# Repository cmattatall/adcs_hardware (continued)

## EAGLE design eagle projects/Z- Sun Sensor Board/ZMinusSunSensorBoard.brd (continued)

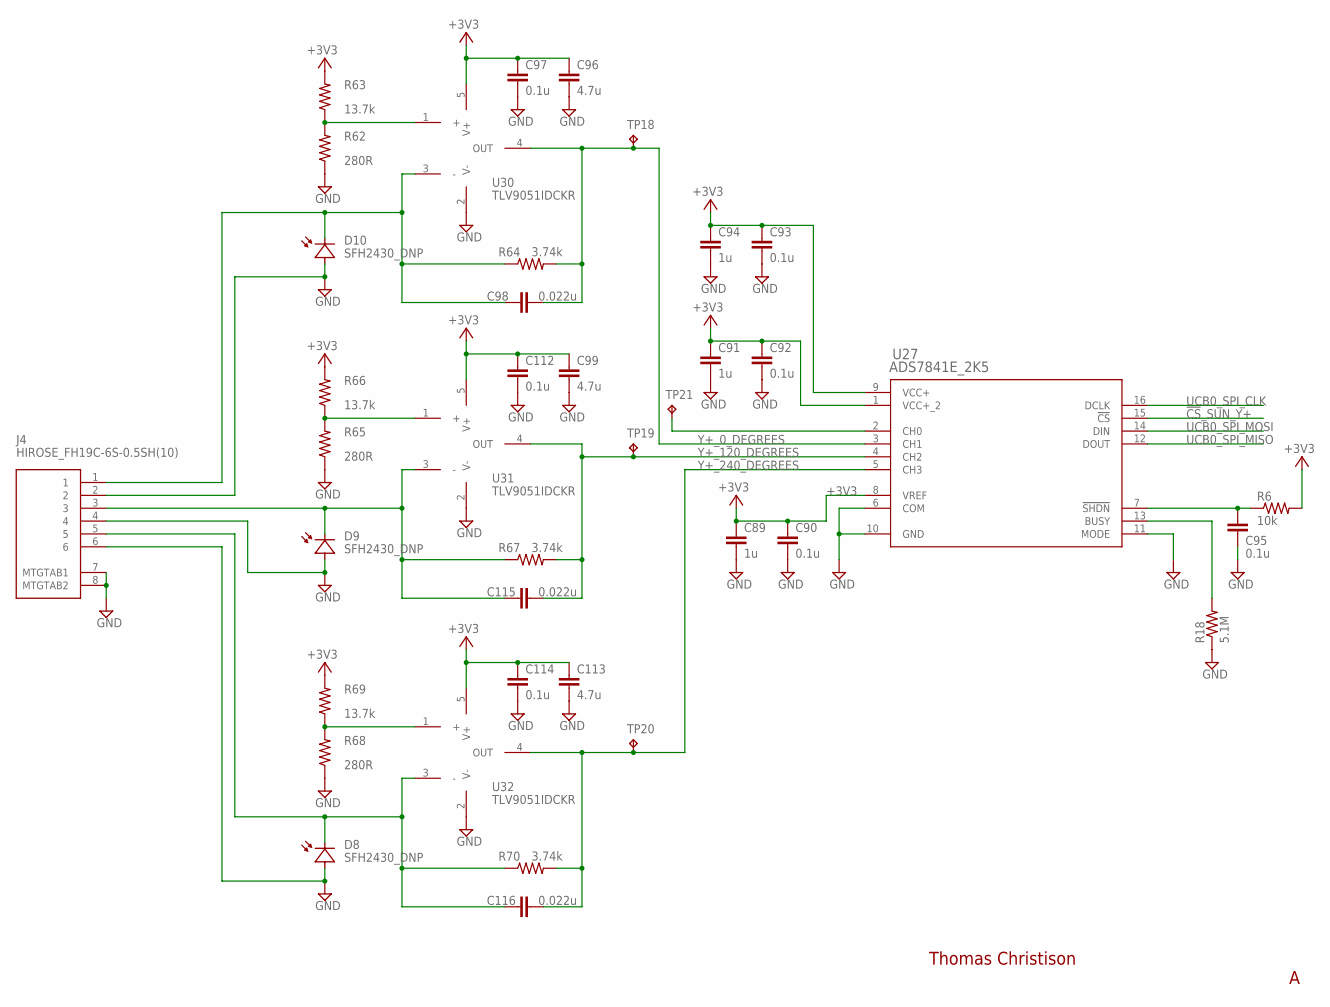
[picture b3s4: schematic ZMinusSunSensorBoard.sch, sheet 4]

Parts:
C89, C91, C94: 1u; C0402
C90, C92, C93, C95, C97, C112, C114: 0.1u; C0402
C96, C99, C113: 4.7u; C0402
C98, C115, C116: 0.022u; C0402
J4: HIROSE_FH19C-6S-0.5SH(10)
R6: 10k; R0402
R18: 5.1M; R0402
R62, R65, R68: 280R; R0402
R63, R66, R69: 13.7k; R0402
R64, R67, R70: 3.74k; R0402
TP18, TP19, TP20, TP21: TESTPOINT; TP_P76H50
U27: ADS7841E_2K5; DBQ16
U30, U31, U32: TLV9051IDCKR; SC70-5P65_210X110L36X22N_TLV9051

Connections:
!CS!_SUN_Y+: U27.15 (!CS); also elsewhere on the board
+3V3: C89.1, C90.1, C91.1, C92.1, C93.1, C94.1, C96.1, C97.1, C99.1, C112.1, C113.1, C114.1, R6.2, R63.2, R66.2, R69.2, U27.1 (VCC+_2), U27.8 (VREF), U27.9 (VCC+), U30.5 (V+), U31.5 (V+), U32.5 (V+); also elsewhere on the board
GND: C89.2, C90.2, C91.2, C92.2, C93.2, C94.2, C95.2, C96.2, C97.2, C99.2, C112.2, C113.2, C114.2, J4.2, J4.4, J4.6, J4.7 (MTGTAB1), J4.8 (MTGTAB2), R18.1, R62.1, R65.1, R68.1, U27.6 (COM), U27.10 (GND), U27.11 (MODE), U30.2 (V-), U31.2 (V-), U32.2 (V-); also elsewhere on the board
unnamed: TP21.1, U27.2 (CH0)
unnamed: C95.1, R6.1, U27.7 (!SHDN)
unnamed: C98.1, J4.1, R64.1, U30.3 (-)
unnamed: R18.2, U27.13 (BUSY)
unnamed: R62.2, R63.1, U30.1 (+)
unnamed: C115.1, J4.3, R67.1, U31.3 (-)
unnamed: R65.2, R66.1, U31.1 (+)
unnamed: C116.1, J4.5, R70.1, U32.3 (-)
unnamed: R68.2, R69.1, U32.1 (+)
UCB0_SPI_CLK: U27.16 (DCLK); also elsewhere on the board
UCB0_SPI_MISO: U27.12 (DOUT); also elsewhere on the board
UCB0_SPI_MOSI: U27.14 (DIN); also elsewhere on the board
Y+_0_DEGREES: C98.2, R64.2, TP18.1, U27.3 (CH1), U30.4 (OUT)
Y+_120_DEGREES: C115.2, R67.2, TP19.1, U27.4 (CH2), U31.4 (OUT)
Y+_240_DEGREES: C116.2, R70.2, TP20.1, U27.5 (CH3), U32.4 (OUT)

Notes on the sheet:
Thomas Christison

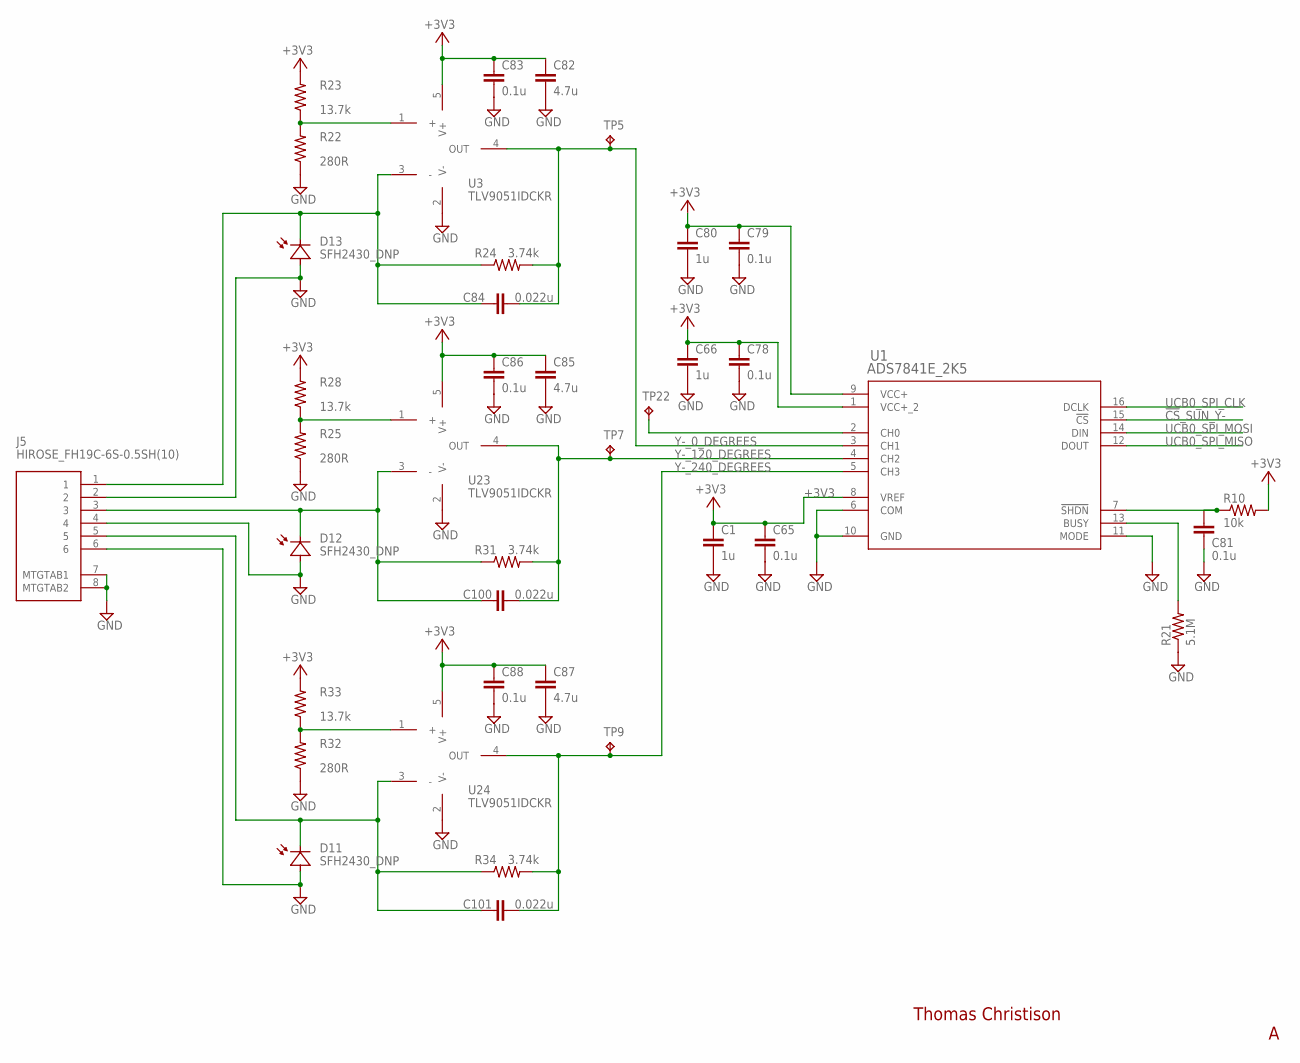
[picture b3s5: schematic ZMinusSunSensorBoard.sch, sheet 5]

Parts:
C1, C66, C80: 1u; C0402
C65, C78, C79, C81, C83, C86, C88: 0.1u; C0402
C82, C85, C87: 4.7u; C0402
C84, C100, C101: 0.022u; C0402
J5: HIROSE_FH19C-6S-0.5SH(10)
R10: 10k; R0402
R21: 5.1M; R0402
R22, R25, R32: 280R; R0402
R23, R28, R33: 13.7k; R0402
R24, R31, R34: 3.74k; R0402
TP5, TP7, TP9, TP22: TESTPOINT; TP_P76H50
U1: ADS7841E_2K5; DBQ16
U3, U23, U24: TLV9051IDCKR; SC70-5P65_210X110L36X22N_TLV9051

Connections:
!CS!_SUN_Y-: U1.15 (!CS); also elsewhere on the board
+3V3: C1.1, C65.1, C66.1, C78.1, C79.1, C80.1, C82.1, C83.1, C85.1, C86.1, C87.1, C88.1, R10.2, R23.2, R28.2, R33.2, U1.1 (VCC+_2), U1.8 (VREF), U1.9 (VCC+), U3.5 (V+), U23.5 (V+), U24.5 (V+); also elsewhere on the board
GND: C1.2, C65.2, C66.2, C78.2, C79.2, C80.2, C81.2, C82.2, C83.2, C85.2, C86.2, C87.2, C88.2, J5.2, J5.4, J5.6, J5.7 (MTGTAB1), J5.8 (MTGTAB2), R21.1, R22.1, R25.1, R32.1, U1.6 (COM), U1.10 (GND), U1.11 (MODE), U3.2 (V-), U23.2 (V-), U24.2 (V-); also elsewhere on the board
unnamed: TP22.1, U1.2 (CH0)
unnamed: C100.1, J5.3, R31.1, U23.3 (-)
unnamed: C81.1, R10.1, U1.7 (!SHDN)
unnamed: C84.1, J5.1, R24.1, U3.3 (-)
unnamed: R22.2, R23.1, U3.1 (+)
unnamed: R25.2, R28.1, U23.1 (+)
unnamed: C101.1, J5.5, R34.1, U24.3 (-)
unnamed: R32.2, R33.1, U24.1 (+)
unnamed: R21.2, U1.13 (BUSY)
UCB0_SPI_CLK: U1.16 (DCLK); also elsewhere on the board
UCB0_SPI_MISO: U1.12 (DOUT); also elsewhere on the board
UCB0_SPI_MOSI: U1.14 (DIN); also elsewhere on the board
Y-_0_DEGREES: C84.2, R24.2, TP5.1, U1.3 (CH1), U3.4 (OUT)
Y-_120_DEGREES: C100.2, R31.2, TP7.1, U1.4 (CH2), U23.4 (OUT)
Y-_240_DEGREES: C101.2, R34.2, TP9.1, U1.5 (CH3), U24.4 (OUT)

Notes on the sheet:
Thomas Christison

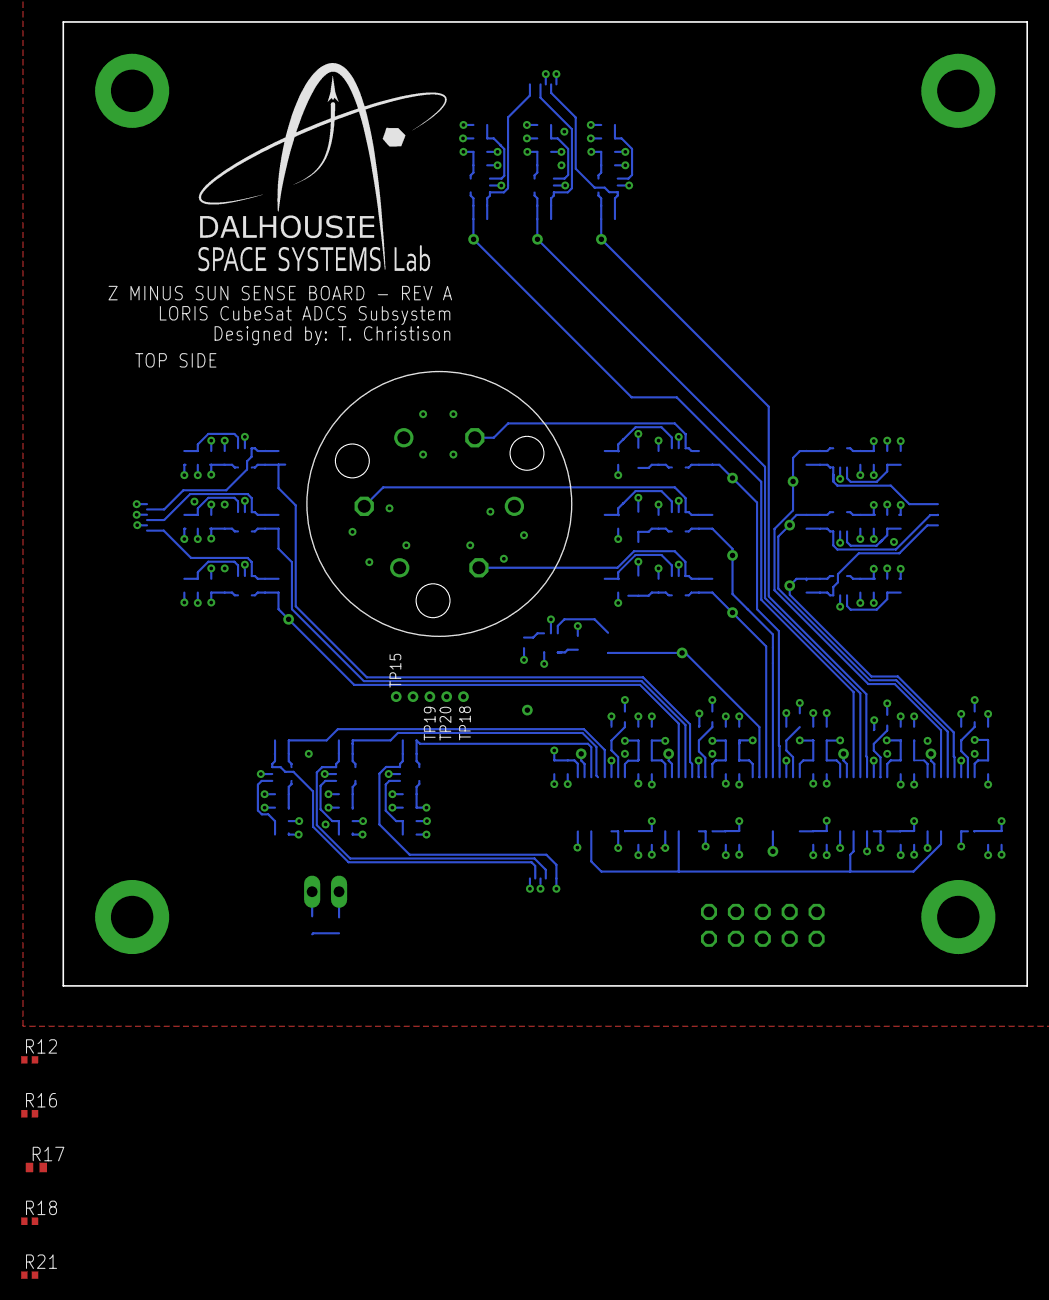
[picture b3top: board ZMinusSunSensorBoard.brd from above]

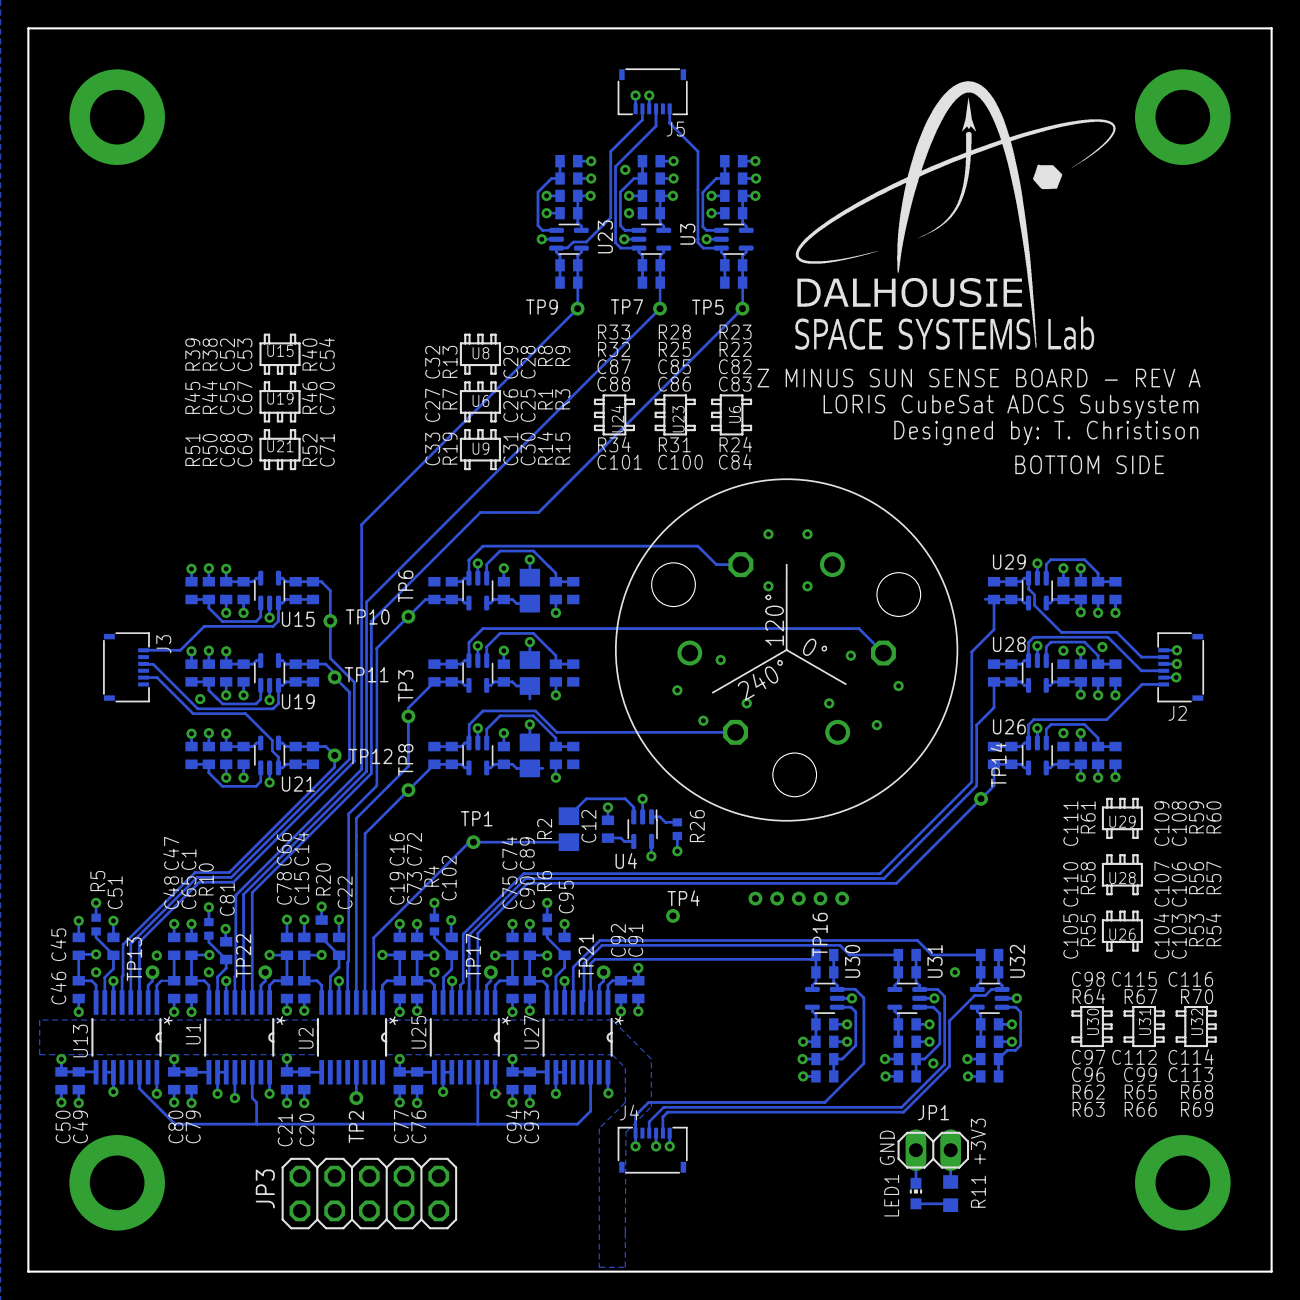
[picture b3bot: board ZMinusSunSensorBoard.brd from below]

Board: 2 copper layers, 91.0 x 91.0 mm, 194 parts (180 on the bottom side), 72 nets.

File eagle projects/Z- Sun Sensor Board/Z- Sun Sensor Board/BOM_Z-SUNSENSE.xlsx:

LORIS ADCS |  |  |  | BILL OF MATERIALS
BOARD: Z- SUN SENSE BOARD |  |  |  | REVISION: A | Date: 2021.01.28
Item | Qty | MPN | Reference Designator | Value | Footprint | Description | Package | Datasheet
1 | 1 | DO NOT POPULATE | A1 | DO NOT POPULATE | Custom | Sun Sensor Mount | SUN_SENOR_MASK | -
2 | 3 | VJ0402Y103KXJAC31 | C14, C16, C21 | 1u | 0402 | CAP CER 10000PF 16V X7R 0402 | C0402 | https://www.vishay.com/docs/45040/vj31vj34automlcc.pdf
3 | 8 | CS0402KRX7R8BB104 | C12, C15, C19, C20, C22, C26, C29, C31 | 0.1u | 0402 | CAP CER 0.1UF 25V X7R 0402 | C0402 | https://www.yageo.com/upload/media/product/productsearch/dat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
4 | 3 | CL21B475KOFNNNE | C25, C28, C30 | 4.7u | 0805 | CAP CER 4.7UF 16V X7R 0805 | C0805 | https://media.digikey.com/pdf/Data%20Sheets/Samsung%20PDFs/C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
5 | 3 | AC0402KRX7R8BB223 | C27, C32, C33 | 0.022u | 0402 | CAP CER 0.022UF 25V X7R 0402 | C0402 | https://www.yageo.com/upload/media/product/productsearch/dat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
6 | 3 | DO NOT POPULATE | J4, J5, J6 | DO NOT POPULATE | DO NOT POPULATE | Terminal Block Connector 1x02 | 2POL254 | -
7 | 1 | DO NOT POPULATE | JP3 | DO NOT POPULATE | DO NOT POPULATE | PIN HEADER | 1X06 | -
8 | 3 | RC0402FR-07280RL | R1, R8, R14 | 280R | 0402 | RES SMD 280 OHM 1% 1/16W 0402 | R0402 | https://www.yageo.com/upload/media/product/productsearch/dat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
9 | 1 | RC0805JR-070RL | R2 | 0R | 0805 | RES SMD 0 OHM JUMPER 1/8W 0805 | R0805 | https://www.yageo.com/upload/media/product/productsearch/dat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
10 | 1 | RE0402FRE0710KL | R20 | 10k | 0402 | RES SMD 10K OHM 1% 1/16W 0402 | R0402 | https://www.yageo.com/upload/media/product/productsearch/dat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
11 | 1 | RC0402JR-075M1L | R26 | 5.1M | 0402 | RES SMD 5.1M OHM 5% 1/16W 0402 | R0603 | https://www.yageo.com/upload/media/product/productsearch/dat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
12 | 3 | RC0402FR-0713K7L | R3, R9, R15 | 13.7k | 0402 | RES SMD 13.7K OHM 1% 1/16W 0402 | R0402 | https://www.yageo.com/upload/media/product/productsearch/dat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
13 | 3 | RC0402FR-073K74L | R7, R13, R19 | 3.74k | 0402 | RES SMD 3.74K OHM 1% 1/16W 0402 | R0402 | https://www.yageo.com/upload/media/product/productsearch/dat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
14 | 1 | ADS7841E | U2 | ADS7841E_2K5 | 16-SSOP | 12 Bit Analog to Digital Converter 4 Input 1 SAR 16-SSOP | DBQ16 | http://www.ti.com/lit/gpn/ADS7841
15 | 1 | LM20BIM7X | U4 | LM20BIM7X_NOPB | SC-70-5 | Temperature Sensor Analog, Local -55°C ~ 130°C 11.77mV/°C SC-70-5 | SOT23-5P65_210X110L40X22N_LM20 | https://www.ti.com/lit/ds/symlink/lm20.pdf?ts=1611799060094&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
16 | 3 | TLV9051IDCKR | U6, U8, U9 | TLV9051IDCKR | SC-70-5 | General Purpose Amplifier 1 Circuit Rail-to-Rail SC-70-5 | SC70-5P65_210X110L36X22N_TLV9051 | https://www.ti.com/lit/ds/symlink/tlv9051.pdf?HQS=dis-dk-nul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

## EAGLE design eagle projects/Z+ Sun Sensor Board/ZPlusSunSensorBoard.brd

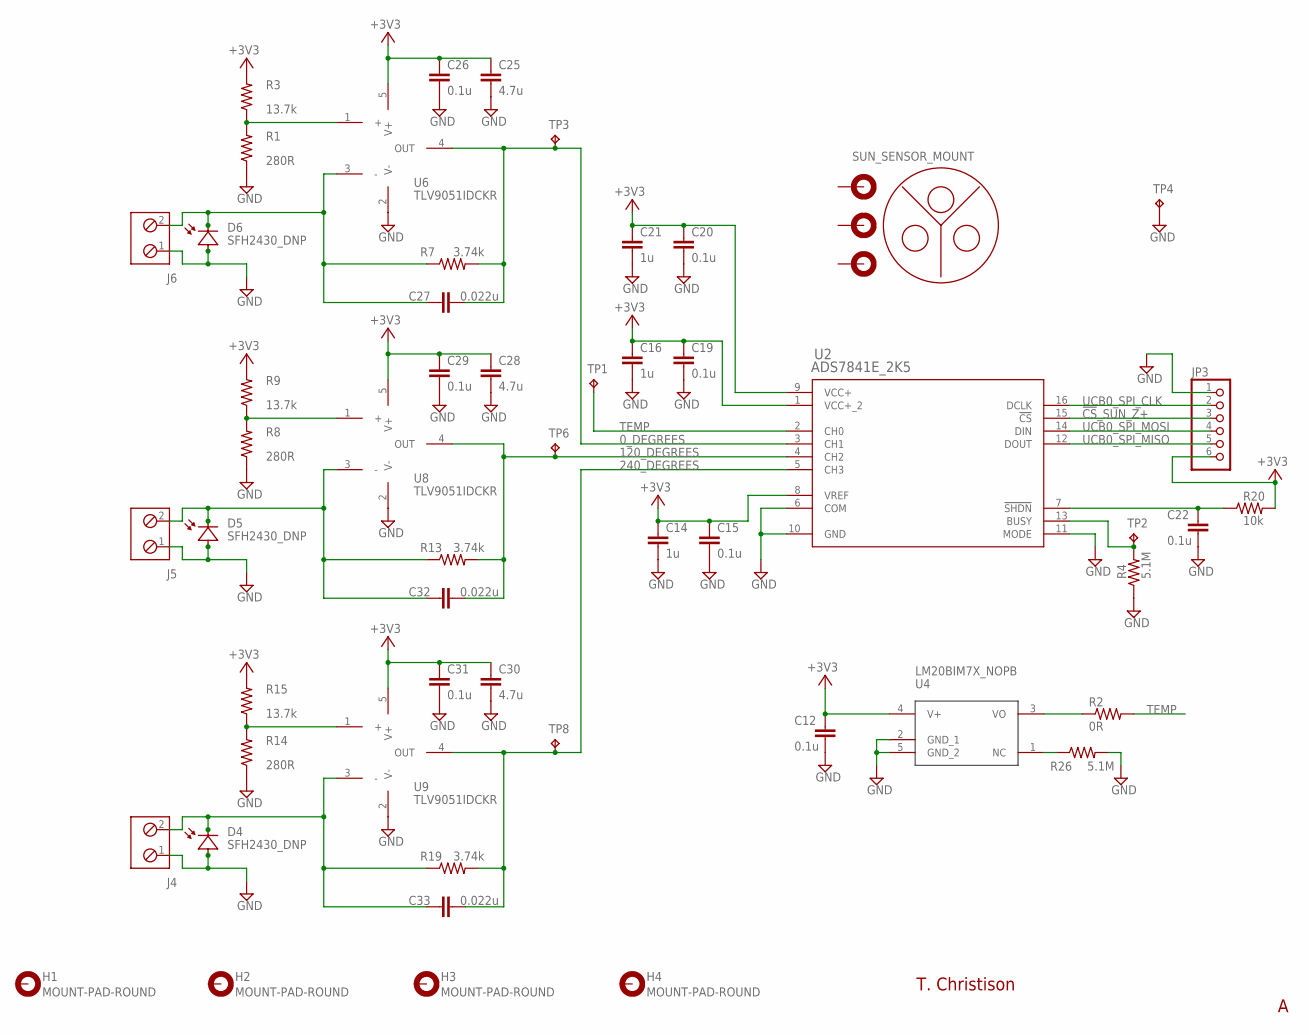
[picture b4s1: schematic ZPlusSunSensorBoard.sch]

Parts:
A1: SUN_SENSOR_MOUNT; SUN_SENOR_MASK
C12, C15, C19, C20, C22, C26, C29, C31: 0.1u; C0402
C14, C16, C21: 1u; C0402
C25, C28, C30: 4.7u; C0805
C27, C32, C33: 0.022u; C0402
H1, H2, H3, H4: MOUNT-PAD-ROUND; PC104
J4, J5, J6: TRM_BLK_1X2; 2POL254
JP3: PINHD-1X6; 1X06
R1, R8, R14: 280R; R0402
R2: 0R; R0805
R3, R9, R15: 13.7k; R0402
R4, R26: 5.1M; R0402
R7, R13, R19: 3.74k; R0402
R20: 10k; R0402
TP1, TP2, TP3, TP4, TP6, TP8: TESTPOINT; TP_P76H50
U2: ADS7841E_2K5; DBQ16
U4: LM20BIM7X_NOPB; SOT23-5P65_210X110L40X22N_LM20
U6, U8, U9: TLV9051IDCKR; SC70-5P65_210X110L36X22N_TLV9051

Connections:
0_DEGREES: C27.2, R7.2, TP3.1, U2.3 (CH1), U6.4 (OUT)
120_DEGREES: C32.2, R13.2, TP6.1, U2.4 (CH2), U8.4 (OUT)
240_DEGREES: C33.2, R19.2, TP8.1, U2.5 (CH3), U9.4 (OUT)
!CS!_SUN_Z+: JP3.3, U2.15 (!CS)
+3V3: C12.1, C14.1, C15.1, C16.1, C19.1, C20.1, C21.1, C25.1, C26.1, C28.1, C29.1, C30.1, C31.1, JP3.6, R3.2, R9.2, R15.2, R20.2, U2.1 (VCC+_2), U2.8 (VREF), U2.9 (VCC+), U4.4 (V+), U6.5 (V+), U8.5 (V+), U9.5 (V+)
GND: C12.2, C14.2, C15.2, C16.2, C19.2, C20.2, C21.2, C22.2, C25.2, C26.2, C28.2, C29.2, C30.2, C31.2, J4.1, J5.1, J6.1, JP3.1, R1.1, R4.1, R8.1, R14.1, R26.2, TP4.1, U2.6 (COM), U2.10 (GND), U2.11 (MODE), U4.2 (GND_1), U4.5 (GND_2), U6.2 (V-), U8.2 (V-), U9.2 (V-)
unnamed: R2.1, U4.3 (VO)
unnamed: R4.2, TP2.1, U2.13 (BUSY)
unnamed: C27.1, J6.2, R7.1, U6.3 (-)
unnamed: R1.2, R3.1, U6.1 (+)
unnamed: R26.1, U4.1 (NC)
unnamed: C32.1, J5.2, R13.1, U8.3 (-)
unnamed: R8.2, R9.1, U8.1 (+)
unnamed: C33.1, J4.2, R19.1, U9.3 (-)
unnamed: R14.2, R15.1, U9.1 (+)
unnamed: C22.1, R20.1, U2.7 (!SHDN)
TEMP: R2.2, TP1.1, U2.2 (CH0)
UCB0_SPI_CLK: JP3.2, U2.16 (DCLK)
UCB0_SPI_MISO: JP3.5, U2.12 (DOUT)
UCB0_SPI_MOSI: JP3.4, U2.14 (DIN)

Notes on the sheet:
T. Christison

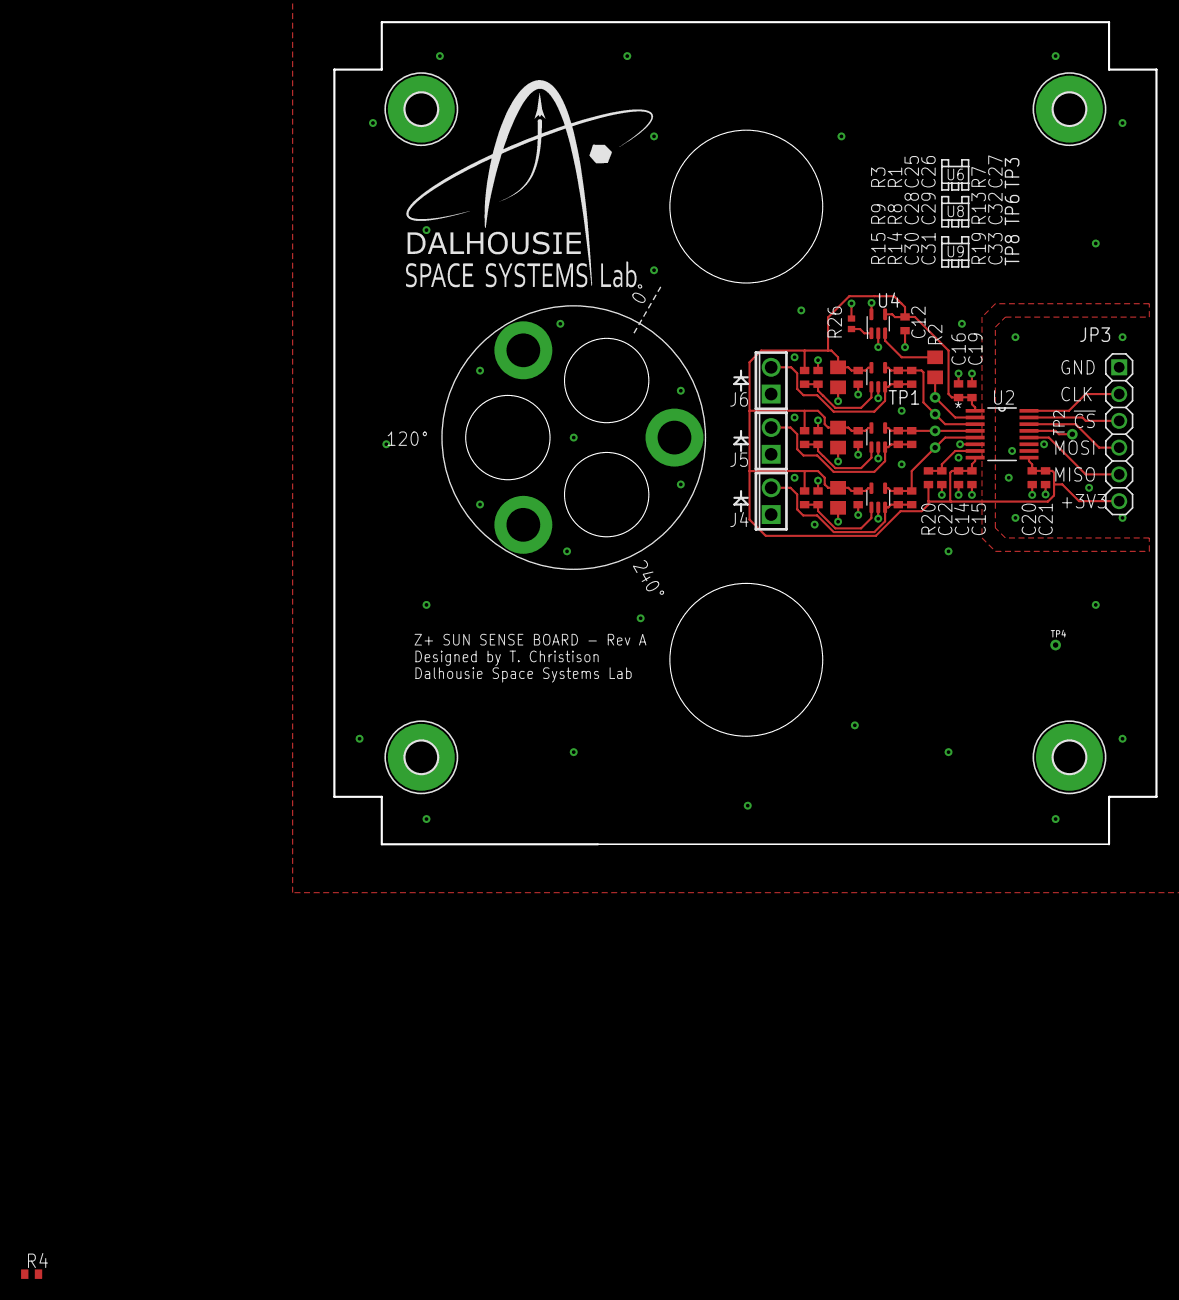
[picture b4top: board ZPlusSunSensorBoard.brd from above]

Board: 2 copper layers, 78.0 x 78.0 mm, 51 parts (0 on the bottom side), 20 nets.

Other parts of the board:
DRILEGEND: DRILEGEND

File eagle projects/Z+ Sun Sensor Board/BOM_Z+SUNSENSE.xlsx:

LORIS ADCS |  |  |  | BILL OF MATERIALS
BOARD: Z+ SUN SENSE BOARD |  |  |  | REV A | Date: 2021.02.14
Item | Qty | MPN | Reference Designator | Value | Footprint | Description | Datasheet
1 | 1 | DO NOT POPULATE | A1 | DO NOT POPULATE | Custom | Sun Sensor Mount | -
2 | 3 | VJ0402Y103KXJAC31 | C14, C16, C21 | 1u | C0402 | CAP CER 10000PF 16V X7R 0402 | https://www.vishay.com/docs/45040/vj31vj34automlcc.pdf
3 | 8 | CS0402KRX7R8BB104 | C12, C15, C19, C20, C22, C26, C29, C31 | 0.1u | C0402 | CAP CER 0.1UF 25V X7R 0402 | https://www.yageo.com/upload/media/product/productsearch/dat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
4 | 3 | CL21B475KOFNNNE | C25, C28, C30 | 4.7u | C0805 | CAP CER 4.7UF 16V X7R 0805 | https://media.digikey.com/pdf/Data%20Sheets/Samsung%20PDFs/C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
5 | 3 | AC0402KRX7R8BB223 | C27, C32, C33 | 0.022u | C0402 | CAP CER 0.022UF 25V X7R 0402 | https://www.yageo.com/upload/media/product/productsearch/dat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
6 | 3 | DO NOT POPULATE | J4, J5, J6 | DO NOT POPULATE | DO NOT POPULATE | Terminal Block Connector 1x02 | -
7 | 1 | DO NOT POPULATE | JP3 | DO NOT POPULATE | DO NOT POPULATE | PIN HEADER | -
8 | 3 | RC0402FR-07280RL | R1, R8, R14 | 280R | R0402 | RES SMD 280 OHM 1% 1/16W 0402 | https://www.yageo.com/upload/media/product/productsearch/dat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
9 | 1 | RC0805JR-070RL | R2 | 0R | R0805 | RES SMD 0 OHM JUMPER 1/8W 0805 | https://www.yageo.com/upload/media/product/productsearch/dat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
10 | 1 | RE0402FRE0710KL | R20 | 10k | R0402 | RES SMD 10K OHM 1% 1/16W 0402 | https://www.yageo.com/upload/media/product/productsearch/dat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
11 | 1 | RC0402JR-075M1L | R26 | 5.1M | R0402 | RES SMD 5.1M OHM 5% 1/16W 0402 | https://www.yageo.com/upload/media/product/productsearch/dat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
12 | 3 | RC0402FR-0713K7L | R3, R9, R15 | 13.7k | R0402 | RES SMD 13.7K OHM 1% 1/16W 0402 | https://www.yageo.com/upload/media/product/productsearch/dat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
13 | 3 | RC0402FR-073K74L | R7, R13, R19 | 5.6k | R0402 | RES SMD 3.74K OHM 1% 1/16W 0402 | https://www.yageo.com/upload/media/product/productsearch/dat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
14 | 1 | ADS7841E | U2 | ADS7841E_2K5 | DBQ16 | 12 Bit Analog to Digital Converter 4 Input 1 SAR 16-SSOP | http://www.ti.com/lit/gpn/ADS7841
15 | 1 | LM20BIM7X | U4 | LM20BIM7X_NOPB | SOT23-5P65_210X110L40X22N_LM20 | Temperature Sensor Analog, Local -55°C ~ 130°C 11.77mV/°C SC-70-5 | https://www.ti.com/lit/ds/symlink/lm20.pdf?ts=1611799060094&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
16 | 3 | TLV9051IDCKR | U6, U8, U9 | TLV9051IDCKR | SC70-5P65_210X110L36X22N_TLV9051 | General Purpose Amplifier 1 Circuit Rail-to-Rail SC-70-5 | https://www.ti.com/lit/ds/symlink/tlv9051.pdf?HQS=dis-dk-nul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

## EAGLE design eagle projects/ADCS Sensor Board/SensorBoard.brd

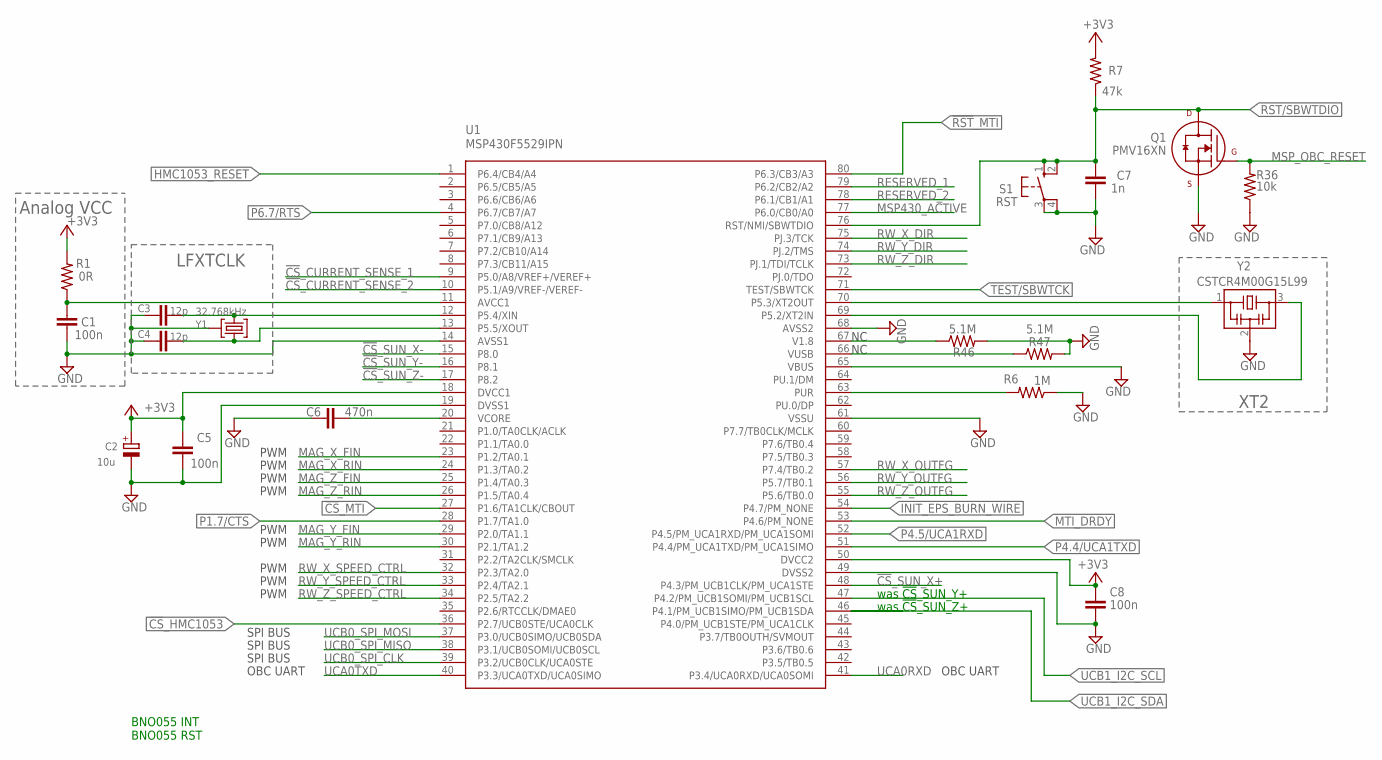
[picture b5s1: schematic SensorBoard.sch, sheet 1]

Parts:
C1, C5, C8: 100n; C0402
C2: 10u; A/3216-18R
C3, C4: 12p; C0402
C6: 470n; C0402
C7: 1n; C0402
Q1: PMV16XN; SOT23-3P95_230X110L20X43N_PMV16XN
R1: 0R; R0402
R6: 1M; R0603
R7: 47k; R0402
R36: 10k; R0603
R46, R47: 5.1M; R0402
S1: RST; B3F-10XX
U1: MSP430F5529IPN; QFP80P50_1400X1400X160L60X22N
Y1: 32.768kHz; MS3V-T1R
Y2: CSTCR4M00G15L99; MURATA-FILTER_CSTCR

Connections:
!CS!_CURRENT_SENSE_1: U1.9 (P5.0/A8/VREF+/VEREF+); also elsewhere on the board
!CS!_CURRENT_SENSE_2: U1.10 (P5.1/A9/VREF-/VEREF-); also elsewhere on the board
!CS!_HMC1053: U1.36 (P2.7/UCB0STE/UCA0CLK); also elsewhere on the board
!CS!_MTI: U1.27 (P1.6/TA1CLK/CBOUT)
!CS!_SUN_X+: U1.48 (P4.3/PM_UCB1CLK/PM_UCA1STE); also elsewhere on the board
!CS!_SUN_X-: U1.15 (P8.0); also elsewhere on the board
!CS!_SUN_Y-: U1.16 (P8.1); also elsewhere on the board
!CS!_SUN_Z-: U1.17 (P8.2); also elsewhere on the board
!RST!_MTI: U1.80 (P6.3/CB3/A3)
+3V3: C2.+, C5.2, C8.1, R1.2, R7.2, U1.18 (DVCC1), U1.50 (DVCC2); also elsewhere on the board
AVCC1: C1.1, R1.1, U1.11 (AVCC1)
GND: C1.2, C2.-, C3.1, C4.1, C5.1, C6.1, C7.2, C8.2, Q1.2 (S), R6.1, R36.1, R46.2, R47.2, S1.3, S1.4 (P1), U1.14 (AVSS1), U1.19 (DVSS1), U1.49 (DVSS2), U1.61 (VSSU), U1.65 (VBUS), U1.68 (AVSS2), Y1.P3 (GND), Y2.2; also elsewhere on the board
HMC1053_RESET: U1.1 (P6.4/CB4/A4); also elsewhere on the board
INIT_EPS_BURN_WIRE: U1.54 (P4.7/PM_NONE)
MAG_X_FIN: U1.23 (P1.2/TA0.1); also elsewhere on the board
MAG_X_RIN: U1.24 (P1.3/TA0.2); also elsewhere on the board
MAG_Y_FIN: U1.29 (P2.0/TA1.1); also elsewhere on the board
MAG_Y_RIN: U1.30 (P2.1/TA1.2); also elsewhere on the board
MAG_Z_FIN: U1.25 (P1.4/TA0.3); also elsewhere on the board
MAG_Z_RIN: U1.26 (P1.5/TA0.4); also elsewhere on the board
MSP430_ACTIVE: U1.77 (P6.0/CB0/A0); also elsewhere on the board
MSP_OBC_RESET: Q1.1 (G), R36.2; also elsewhere on the board
MTI_DRDY: U1.53 (P4.6/PM_NONE)
unnamed: R46.1, U1.67 (V1.8)
unnamed: R47.1, U1.66 (VUSB)
P1.7/CTS: U1.28 (P1.7/TA1.0); also elsewhere on the board
P4.4/UCA1TXD: U1.51 (P4.4/PM_UCA1TXD/PM_UCA1SIMO); also elsewhere on the board
P4.5/UCA1RXD: U1.52 (P4.5/PM_UCA1RXD/PM_UCA1SOMI); also elsewhere on the board
P5.2/XT2IN1: U1.69 (P5.2/XT2IN), Y2.3
P5.3/XT2OUT1: U1.70 (P5.3/XT2OUT), Y2.1
P5.4/XIN1: C3.2, U1.12 (P5.4/XIN), Y1.P2 (2)
P5.5/XOUT1: C4.2, U1.13 (P5.5/XOUT), Y1.P1 (1)
P6.7/RTS: U1.4 (P6.7/CB7/A7); also elsewhere on the board
RESERVED_1: U1.79 (P6.2/CB2/A2); also elsewhere on the board
RESERVED_2: U1.78 (P6.1/CB1/A1); also elsewhere on the board
RST/SBWTDIO: C7.1, Q1.3 (D), R7.1, S1.1 (S), S1.2 (S1), U1.76 (RST/NMI/SBWTDIO); also elsewhere on the board
RW_X_DIR: U1.75 (PJ.3/TCK); also elsewhere on the board
RW_X_OUTFG: U1.57 (P7.4/TB0.2); also elsewhere on the board
RW_X_SPEED_CTRL: U1.32 (P2.3/TA2.0); also elsewhere on the board
RW_Y_DIR: U1.74 (PJ.2/TMS); also elsewhere on the board
RW_Y_OUTFG: U1.56 (P5.7/TB0.1); also elsewhere on the board
RW_Y_SPEED_CTRL: U1.33 (P2.4/TA2.1); also elsewhere on the board
RW_Z_DIR: U1.73 (PJ.1/TDI/TCLK); also elsewhere on the board
RW_Z_OUTFG: U1.55 (P5.6/TB0.0); also elsewhere on the board
RW_Z_SPEED_CTRL: U1.34 (P2.5/TA2.2); also elsewhere on the board
TARGET_PUR: R6.2, U1.63 (PUR)
TEST/SBWTCK: U1.71 (TEST/SBWTCK); also elsewhere on the board
UCA0RXD: U1.41 (P3.4/UCA0RXD/UCA0SOMI); also elsewhere on the board
UCA0TXD: U1.40 (P3.3/UCA0TXD/UCA0SIMO); also elsewhere on the board
UCB0_SPI_CLK: U1.39 (P3.2/UCB0CLK/UCA0STE); also elsewhere on the board
UCB0_SPI_MISO: U1.38 (P3.1/UCB0SOMI/UCB0SCL); also elsewhere on the board
UCB0_SPI_MOSI: U1.37 (P3.0/UCB0SIMO/UCB0SDA); also elsewhere on the board
UCB1_I2C_SCL: U1.47 (P4.2/PM_UCB1SOMI/PM_UCB1SCL); also elsewhere on the board
UCB1_I2C_SDA: U1.46 (P4.1/PM_UCB1SIMO/PM_UCB1SDA); also elsewhere on the board
VCORE1: C6.2, U1.20 (VCORE)

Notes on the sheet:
LFXTCLK
XT2
Analog VCC
PWM
OBC UART
SPI BUS
was !CS!_SUN_Y+
was !CS!_SUN_Z+
BNO055 INT BNO055 RST

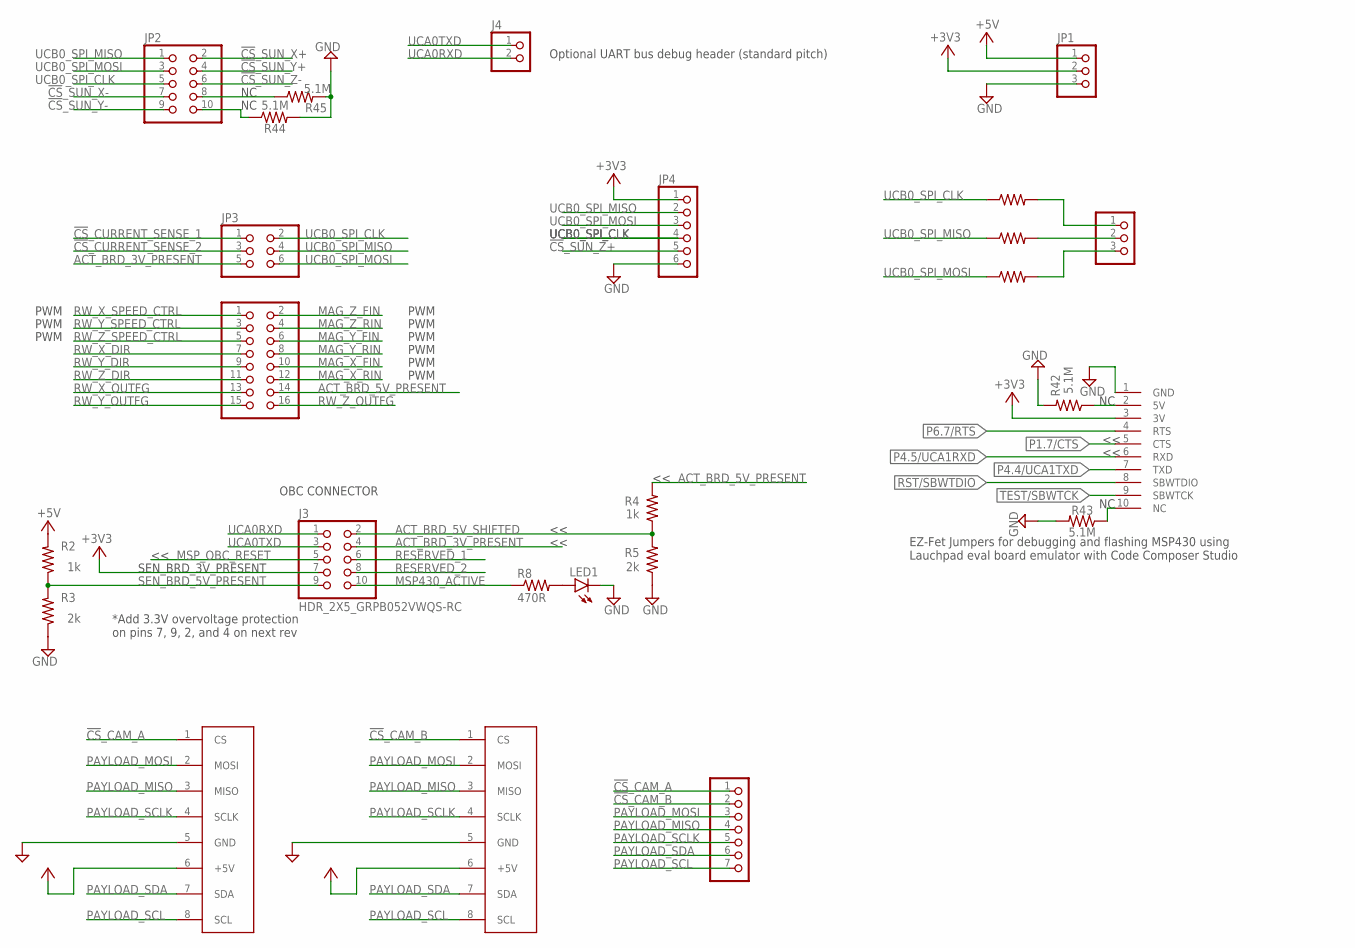
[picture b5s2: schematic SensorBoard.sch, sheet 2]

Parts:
A2, A3: ARDUCAM_OV5642; ARDUCAM
J1: HDR_10_EZFET_DEBUGGER; HDRV10W66P254_10X1_2540X254H858
J3: HDR_2X5_GRPB052VWQS-RC; GRPB052VWQS-RC
J4: HDR_1X2_; 1X02
J6: PINHD-2X8; 2X08
J10: PINHD-1X3; 1X03
J11: PINHD-1X7; 1X07
JP1: PINHD-1X3; 1X03
JP2: PINHD-2X5; 2X05
JP3: PINHD-2X3; 2X03
JP4: PINHD-1X6; 1X06
LED1: LEDCHIP-LED0603; CHIP-LED0603
R2, R4: 1k; R0603
R3, R5: 2k; R0603
R8: 470R; R0603
R33, R34, R35: 0R; R0805
R42, R43, R44, R45: 5.1M; R0402

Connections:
!CS!_CAM_A: A2.1 (CS), J11.1
!CS!_CAM_B: A3.1 (CS), J11.2
!CS!_CURRENT_SENSE_1: JP3.1; also elsewhere on the board
!CS!_CURRENT_SENSE_2: JP3.3; also elsewhere on the board
!CS!_SUN_X+: JP2.2; also elsewhere on the board
!CS!_SUN_X-: JP2.7; also elsewhere on the board
!CS!_SUN_Y+: JP2.4
!CS!_SUN_Y-: JP2.9; also elsewhere on the board
!CS!_SUN_Z+: JP4.5
!CS!_SUN_Z-: JP2.6; also elsewhere on the board
+3V3: J1.3 (3V), J3.7, JP1.2, JP4.1; also elsewhere on the board
+5V: A2.6 (+5V), A3.6 (+5V), JP1.1, R2.2; also elsewhere on the board
ACT_BRD_3V_PRESENT: J3.4, JP3.5
ACT_BRD_5V_PRESENT: J6.14, R4.2
ACT_BRD_5V_SHIFTED: J3.2, R4.1, R5.2
GND: A2.5 (GND), A3.5 (GND), J1.1 (GND), JP1.3, JP4.6, LED1.C, R3.1, R5.1, R42.2, R43.2, R44.2, R45.2; also elsewhere on the board
MAG_X_FIN: J6.10; also elsewhere on the board
MAG_X_RIN: J6.12; also elsewhere on the board
MAG_Y_FIN: J6.6; also elsewhere on the board
MAG_Y_RIN: J6.8; also elsewhere on the board
MAG_Z_FIN: J6.2; also elsewhere on the board
MAG_Z_RIN: J6.4; also elsewhere on the board
MSP430_ACTIVE: J3.10, R8.1; also elsewhere on the board
MSP_OBC_RESET: J3.5; also elsewhere on the board
unnamed: J10.1, R33.2
unnamed: J10.2, R34.2
unnamed: J10.3, R35.2
unnamed: LED1.A, R8.2
unnamed: JP2.8, R45.1
unnamed: JP2.10, R44.1
unnamed: J1.2 (5V), R42.1
unnamed: J1.10 (NC), R43.1
P1.7/CTS: J1.5 (CTS); also elsewhere on the board
P4.4/UCA1TXD: J1.7 (TXD); also elsewhere on the board
P4.5/UCA1RXD: J1.6 (RXD); also elsewhere on the board
P6.7/RTS: J1.4 (RTS); also elsewhere on the board
PAYLOAD_MISO: A2.3 (MISO), A3.3 (MISO), J11.4
PAYLOAD_MOSI: A2.2 (MOSI), A3.2 (MOSI), J11.3
PAYLOAD_SCL: A2.8 (SCL), A3.8 (SCL), J11.7
PAYLOAD_SCLK: A2.4 (SCLK), A3.4 (SCLK), J11.5
PAYLOAD_SDA: A2.7 (SDA), A3.7 (SDA), J11.6
RESERVED_1: J3.6; also elsewhere on the board
RESERVED_2: J3.8; also elsewhere on the board
RST/SBWTDIO: J1.8 (SBWTDIO); also elsewhere on the board
RW_X_DIR: J6.7; also elsewhere on the board
RW_X_OUTFG: J6.13; also elsewhere on the board
RW_X_SPEED_CTRL: J6.1; also elsewhere on the board
RW_Y_DIR: J6.9; also elsewhere on the board
RW_Y_OUTFG: J6.15; also elsewhere on the board
RW_Y_SPEED_CTRL: J6.3; also elsewhere on the board
RW_Z_DIR: J6.11; also elsewhere on the board
RW_Z_OUTFG: J6.16; also elsewhere on the board
RW_Z_SPEED_CTRL: J6.5; also elsewhere on the board
SEN_BRD_5V_PRESENT: J3.9, R2.1, R3.2
TEST/SBWTCK: J1.9 (SBWTCK); also elsewhere on the board
UCA0RXD: J3.1, J4.2; also elsewhere on the board
UCA0TXD: J3.3, J4.1; also elsewhere on the board
UCB0_SPI_CLK: JP2.5, JP3.2, JP4.4, R33.1; also elsewhere on the board
UCB0_SPI_MISO: JP2.1, JP3.4, JP4.2, R34.1; also elsewhere on the board
UCB0_SPI_MOSI: JP2.3, JP3.6, JP4.3, R35.1; also elsewhere on the board

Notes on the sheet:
PWM
OBC CONNECTOR
SEN_BRD_3V_PRESENT
*Add 3.3V overvoltage protection on pins 7, 9, 2, and 4 on next rev
EZ-Fet Jumpers for debugging and flashing MSP430 using Lauchpad eval board emulator with Code Composer Studio
Optional UART bus debug header (standard pitch)
